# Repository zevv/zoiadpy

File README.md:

# Experimental external display for the Empress Zoia

The repo holds the source code and schematics/pcb design for an external
display for the Zoia. The Zoia comes with a screen so small you can cover it
with the tip of your pinky. This is barely usable when prgramming the Zoia on
your couch, but totally useless on stage when changing programs or parameters.

This external display hooks onto the SPI bus between the Zoia en the tiny OLED
display and sniffs the screen contents when the display is updated. The screen
is upscaled to 480x320 resolution and sent to a second larger display.

The Zoia luckily exposes the OLED SPI on a friendly 2.54mm header row, so
anyone with basic soldering skills should be able to connect some wires to
these and feed them out of the box. I used a retro style DB9 type connector
for this myself, as this happened to be available in my parts drawer. You
need 5 wires in total, so any connector with enough pins should do:

- GND
- VCC
- MOSI
- CLK
- CS

# Disclaimer

I love this little project for me personally, but I do not recommend others to
go hack their Zoia: you will surely void the warranty of your box, and it is
very possible it will break in the process of adding the screen. Do not
complain to me when this happens.

# Software

Not too complicated: ESP32 has a bunch of SPI busses and supports both master
and slave mode. The OLED SPI is running in slave mode and handles all SPI
transfers of exactly 1024 bytes, as these contain the full updated screen data.
All other SPI transfers are simply ignored, as these contain the usual setup
parameters for the display.

The second SPI runs in master mode and drives an ILI4822 type TFT display which
I happened to have lying around. Although this is a full color display, it's
driven in 3 bits per pixel mode only to allow the big screen to keep up with
the OLED frame rate.

# Hardware

Kicad schematics and PCB design are available, but I have not yet produced this
as I'm happy to run on my current prototype hardware. I'm sure these are mostly
ok but someone will have to actually build and test these to make sure. I might
do this one day.

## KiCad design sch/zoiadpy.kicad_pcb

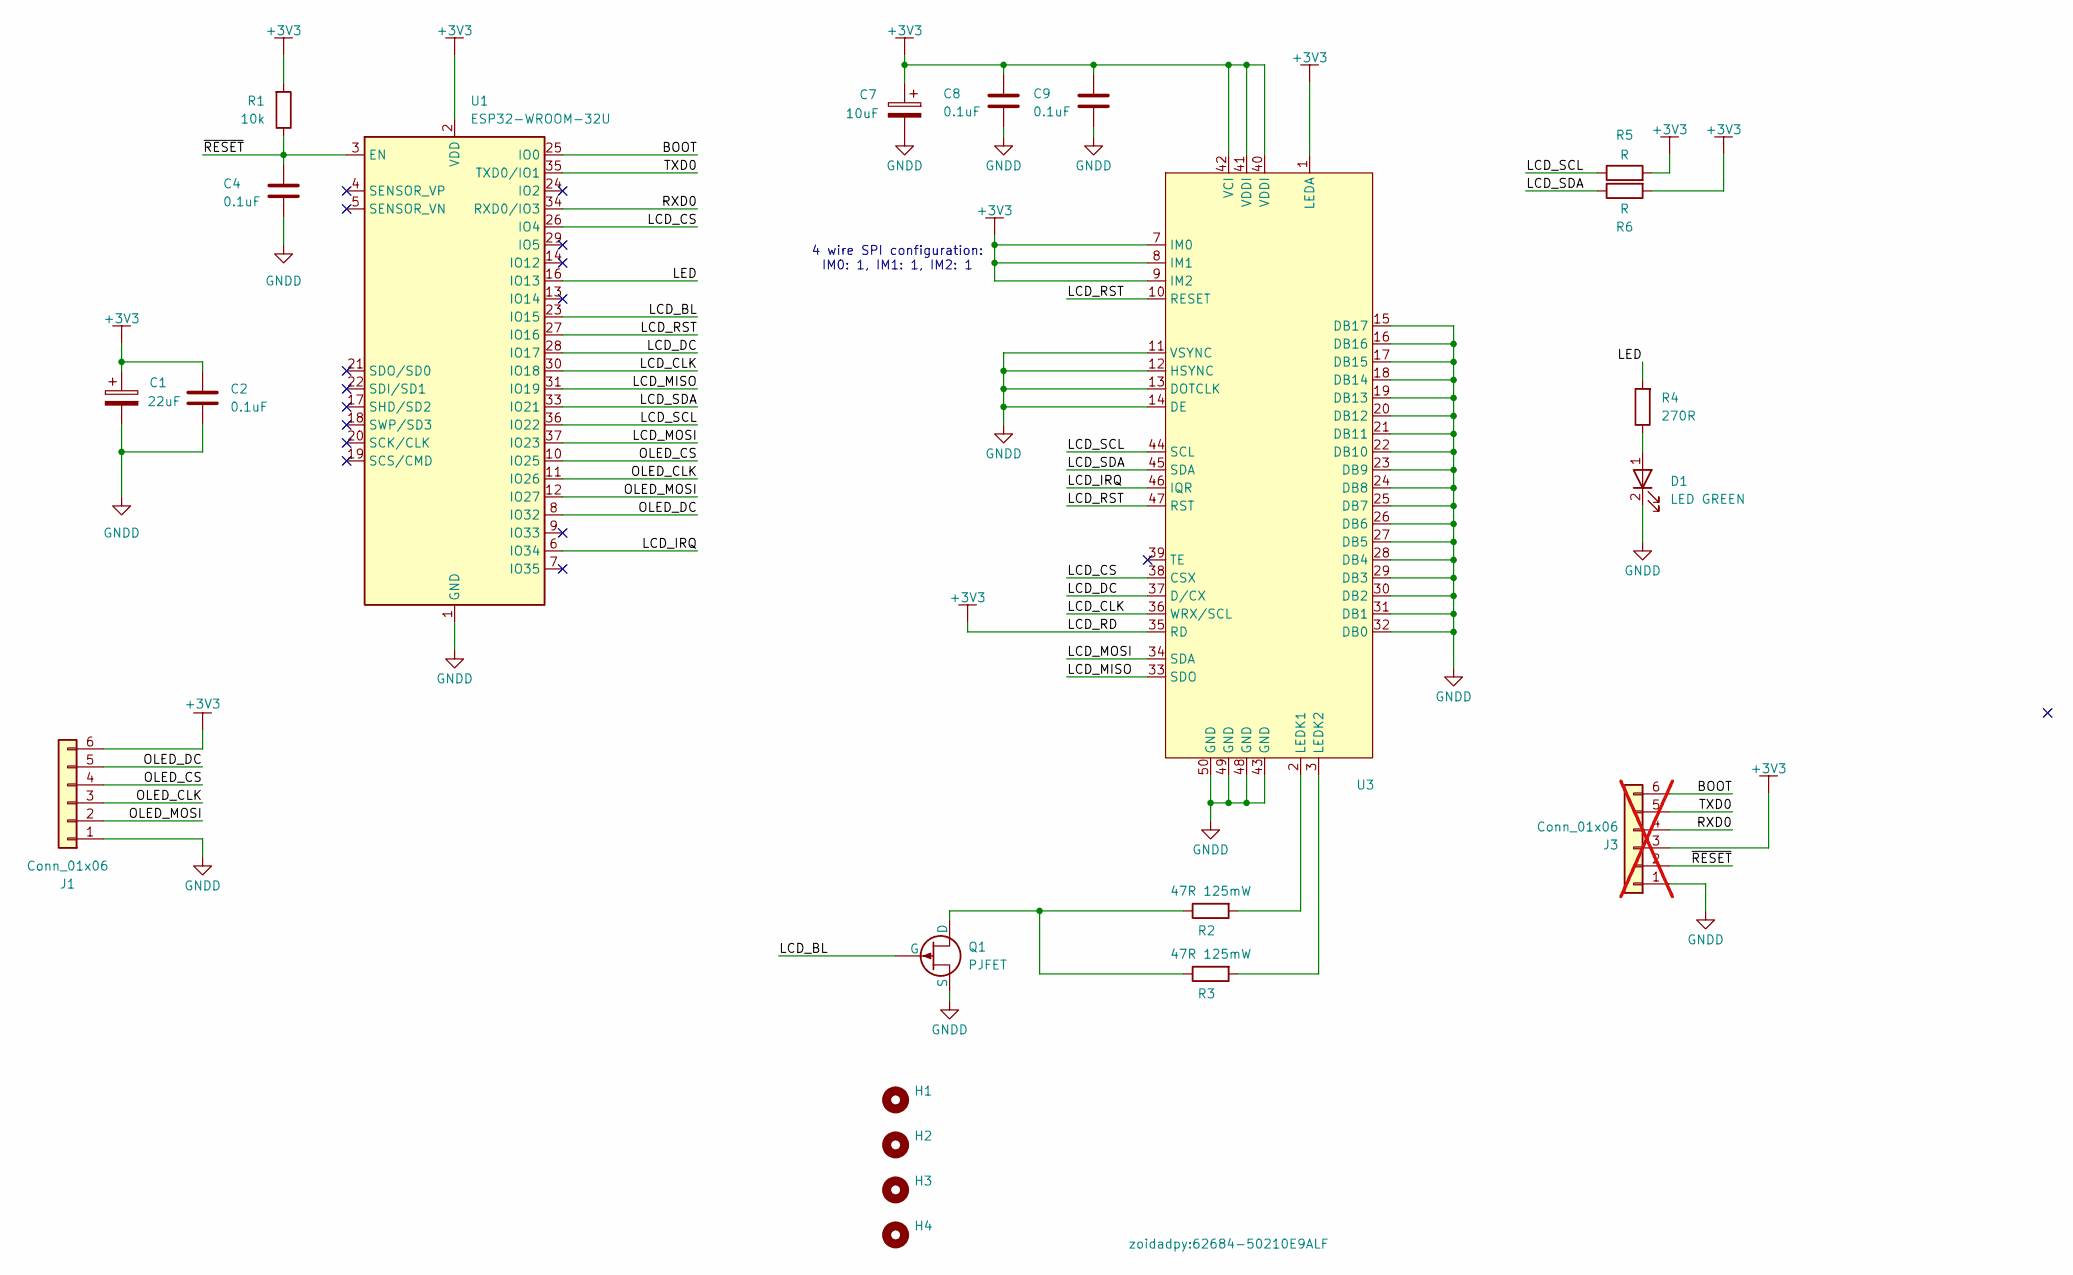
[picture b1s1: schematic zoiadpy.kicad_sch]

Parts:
C1: 22uF; CP_EIA-2012-12_Kemet-R; JLC C5674
C2, C4, C8, C9: 0.1uF; C_0603_1608Metric
C7: 10uF; CP_EIA-2012-12_Kemet-R; JLC C5674
D1: LED GREEN; LED_0603_1608Metric
H1, H2, H3, H4: MountingHole; MountingHole_3.2mm_M3
J1: Conn_01x06; PinHeader_1x06_P2.54mm_Horizontal
J3: Conn_01x06; PinHeader_1x06_P2.54mm_Vertical; not fitted
Q1: PJFET
R1: 10k; R_0603_1608Metric
R2, R3: 47R 125mW; R_0805_2012Metric
R4: 270R; R_0603_1608Metric; Farnell 2141320
R5, R6: R; R_0603_1608Metric
U1: ESP32-WROOM-32U
U3: 62684-50210E9ALF

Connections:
+3V3: C1.1, C2.1, C7.1, C8.1, C9.1, J1.6, J3.3, R1.2, R5.2, R6.2, U1.2 (VDD), U3.1 (LEDA), U3.7 (IM0), U3.8 (IM1), U3.9 (IM2), U3.35 (RD), U3.40 (VDDI), U3.41 (VDDI), U3.42 (VCI)
/BOOT: J3.6, U1.25 (IO0)
/LCD_BL: Q1.2 (G), U1.23 (IO15)
/LCD_CLK: U1.30 (IO18), U3.36 (WRX/SCL)
/LCD_CS: U1.26 (IO4), U3.38 (CSX)
/LCD_DC: U1.28 (IO17), U3.37 (D/CX)
/LCD_IRQ: U1.6 (IO34), U3.46 (IQR)
/LCD_MISO: U1.31 (IO19), U3.33 (SDO)
/LCD_MOSI: U1.37 (IO23), U3.34 (SDA)
/LCD_RST: U1.27 (IO16), U3.10 (RESET), U3.47 (RST)
/LCD_SCL: R5.1, U1.36 (IO22), U3.44 (SCL)
/LCD_SDA: R6.1, U1.33 (IO21), U3.45 (SDA)
/LED: R4.2, U1.16 (IO13)
/OLED_CLK: J1.3, U1.11 (IO26)
/OLED_CS: J1.4, U1.10 (IO25)
/OLED_DC: J1.5, U1.8 (IO32)
/OLED_MOSI: J1.2, U1.12 (IO27)
/RXD0: J3.4, U1.34 (RXD0/IO3)
/TXD0: J3.5, U1.35 (TXD0/IO1)
/~RESET: C4.1, J3.2, R1.1, U1.3 (EN)
GNDD: C1.2, C2.2, C4.2, C7.2, C8.2, C9.2, D1.2 (K), J1.1, J3.1, Q1.3 (S), U1.1 (GND), U1.15 (GND), U1.38 (GND), U1.39 (GND), U3.11 (VSYNC), U3.12 (HSYNC), U3.13 (DOTCLK), U3.14 (DE), U3.15 (DB17), U3.16 (DB16), U3.17 (DB15), U3.18 (DB14), U3.19 (DB13), U3.20 (DB12), U3.21 (DB11), U3.22 (DB10), U3.23 (DB9), U3.24 (DB8), U3.25 (DB7), U3.26 (DB6), U3.27 (DB5), U3.28 (DB4), U3.29 (DB3), U3.30 (DB2), U3.31 (DB1), U3.32 (DB0), U3.43 (GND), U3.48 (GND), U3.49 (GND), U3.50 (GND)
unnamed: D1.1 (A), R4.1
unnamed: Q1.1 (D), R2.1, R3.1
unnamed: R2.2, U3.2 (LEDK1)
unnamed: R3.2, U3.3 (LEDK2)

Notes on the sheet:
4 wire SPI configuration: IM0: 1, IM1: 1, IM2: 1

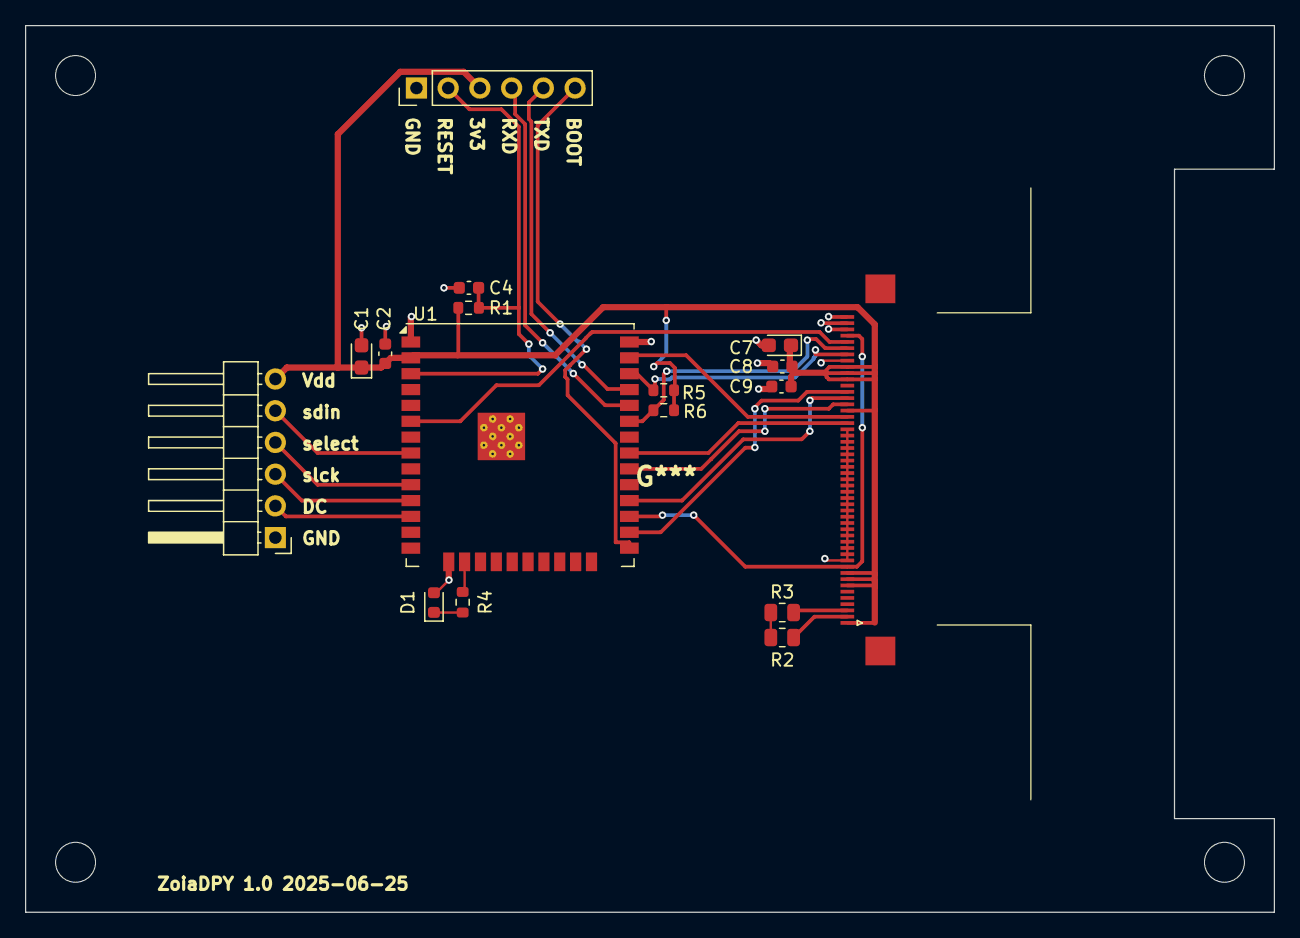
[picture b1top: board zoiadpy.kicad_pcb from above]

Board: 2 copper layers, 100.0 x 71.0 mm, 21 parts (0 on the bottom side), 24 nets.

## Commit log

2025-06-23 Initial checkin, decoding to uart works on ESP32
2025-06-23 updated SPI gpios
2025-06-24 2pbb
2025-06-24 rgb666
2025-06-24 optimized fb xform
2025-06-24 dropped lvgl
2025-06-24 nice
2025-06-24 nice2
2025-06-24 cleanups
2025-06-24 looks good
2025-06-24 nicer
2025-06-25 Added schematics and pcB
2025-06-25 REAMDE
2025-06-28 changed spi buffer handling to avoid rx overruns
2025-06-28 limit lcd to 33 fps
2025-07-04 more spi
2025-07-04 Once more refactored to get the DMA to behave
